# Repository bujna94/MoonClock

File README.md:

### Hi there, I'm Pavol 👋 

### MoonClock website - https://moonclock.com

## You have received and unboxed your MoonClock. Congratulations!

What now?

1. Plug MoonClock into your computer with provided USB-C cable. It will appear as a standard USB drive called "MOONCLOCK".

2. Open "secrets.py" with a text editor such as notepad and replace "WIFI_SSID" and "WIFI_PASSWORD" with your WiFi details and save.

3. Wait ~2minutes until Bitcoin price will appear on the MoonClock device.

That's all!

## Want more Crypto or just adjust the settings?

We all love Bitcoin, sure, but maybe you want to see the current price in another currency or completely another Crypto? No problem. MoonClock is ready for that!

1. Plug MoonClock into your computer with provided USB-C cable. It will appear as a standard USB drive called "MOONCLOCK".

2. Remove all files & folders from the "MOONCLOCK" drive.

3. Configure your cryptocurrencies in conf.py and copy the content of the MOONCLOCK folder to the "MOONCLOCK" USB drive. (Don't forget to change your WiFi details again in the "secrets.py" file if you have to)

Wait ~2 minutes until new crypto will be shown on MoonClock.

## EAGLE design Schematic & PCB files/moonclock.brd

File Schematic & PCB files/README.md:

### The new schematic and PCB design

### Schematic

These are the final schematics using ESP32-S2.

### Main Board:

### USB Board Schematic:

### PCB Design

Here you can see the PCB design currently in manufacture 

### Main Board:

### USB Board:

### PCB view

This is the PCB view from OSH Park (but will be manufactured by JLCPCB).

### Main Board:

### USB Board:

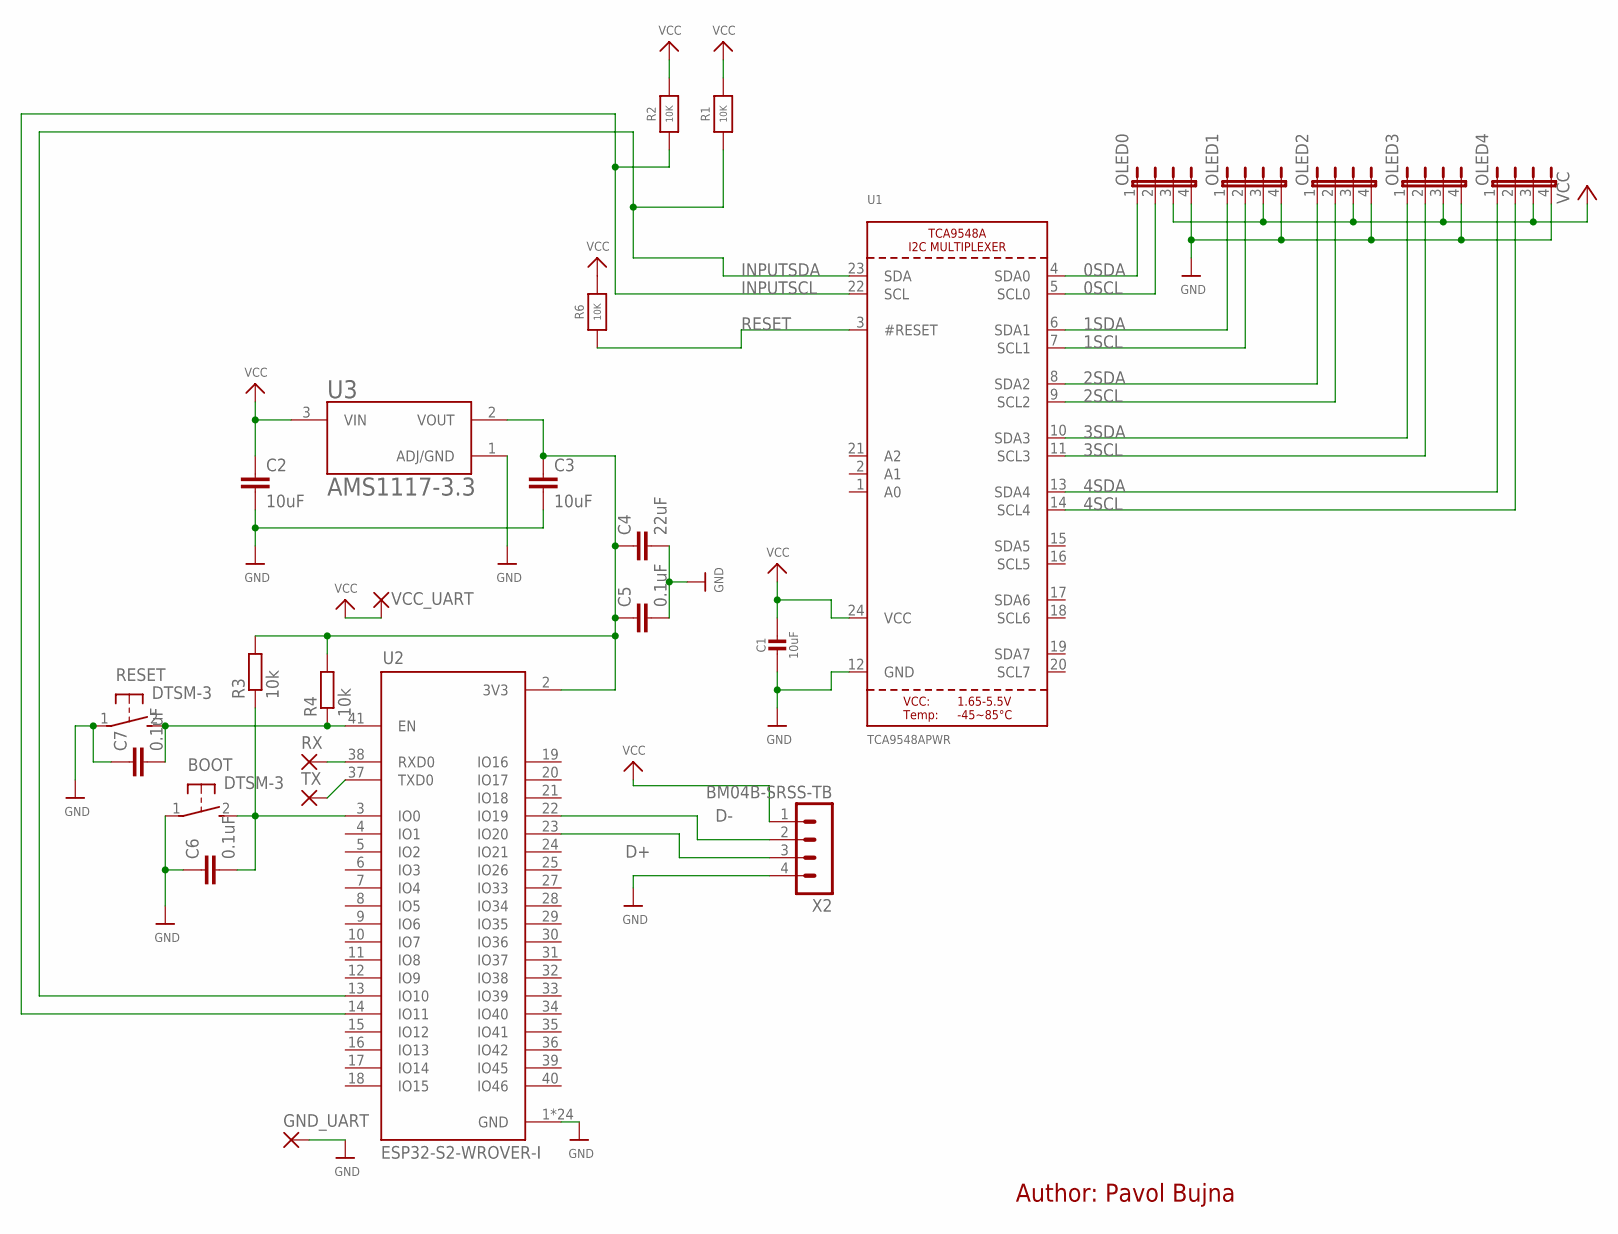
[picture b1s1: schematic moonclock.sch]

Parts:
BOOT: DTSM-3
C1: 10uF; 0805-NO
C2, C3: 10uF; C0805
C4: 22uF; C0805
C5, C6, C7: 0.1uF; C0805
GND_UART: SMD2; SMD1,27-2,54
OLED0, OLED1, OLED2, OLED3, OLED4: JP4E; JP4
R1, R2: 10K; 0805-NO
R3, R4: 10k; R0805
R6: 10K; _0805MP
RESET: DTSM-3
RX: SMD2; SMD1,27-2,54
TX: SMD2; SMD1,27-2,54
U1: TCA9548APWR; TSSOP24
U2: ESP32-S2-WROVER-I
U3: AMS1117-3.3; SOT229P700X180-4N
VCC_UART: SMD2; SMD1,27-2,54
X2: BM04B-SRSS-TB

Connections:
0SCL: OLED0.2, U1.5 (SCL0)
0SDA: OLED0.1, U1.4 (SDA0)
1SCL: OLED1.2, U1.7 (SCL1)
1SDA: OLED1.1, U1.6 (SDA1)
2SCL: OLED2.2, U1.9 (SCL2)
2SDA: OLED2.1, U1.8 (SDA2)
3SCL: OLED3.2, U1.11 (SCL3)
3SDA: OLED3.1, U1.10 (SDA3)
4SCL: OLED4.2, U1.14 (SCL4)
4SDA: OLED4.1, U1.13 (SDA4)
D+: U2.23 (IO20), X2.3
D-: U2.22 (IO19), X2.2
GND: BOOT.1, C1.2, C2.2, C3.2, C4.2, C5.2, C6.1, C7.1, GND_UART.1, OLED0.4, OLED1.4, OLED2.4, OLED3.4, OLED4.4, RESET.1, U1.12 (GND), U2.1 (GND), U2.26 (GND), U2.42 (GND), U2.43.1 (GND), U2.43.2 (GND), U2.43.3 (GND), U2.43.4 (GND), U2.43.5 (GND), U2.43.6 (GND), U2.43.7 (GND), U2.43.8 (GND), U2.43.9 (GND), U2.43.10 (GND), U2.43.11 (GND), U2.43.12 (GND), U2.43.13 (GND), U2.43.14 (GND), U2.43.15 (GND), U2.43.16 (GND), U2.43.17 (GND), U2.43.18 (GND), U2.43.19 (GND), U2.43.20 (GND), U2.43.21 (GND), U3.1 (ADJ/GND), X2.4
INPUTSCL: R2.1, U1.22 (SCL), U2.14 (IO11)
INPUTSDA: R1.1, U1.23 (SDA), U2.13 (IO10)
unnamed: TX.1, U2.37 (TXD0)
unnamed: RX.1, U2.38 (RXD0)
unnamed: C3.1, C4.1, C5.1, R3.2, R4.2, U2.2 (3V3), U3.2 (VOUT)
unnamed: BOOT.2, C6.2, R3.1, U2.3 (IO0)
unnamed: C7.2, R4.1, RESET.2, U2.41 (EN)
RESET: R6.1, U1.3 (#RESET)
VCC: C1.1, C2.1, OLED0.3, OLED1.3, OLED2.3, OLED3.3, OLED4.3, R1.2, R2.2, R6.2, U1.24 (VCC), U3.3 (VIN), VCC_UART.1, X2.1

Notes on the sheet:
Author: Pavol Bujna

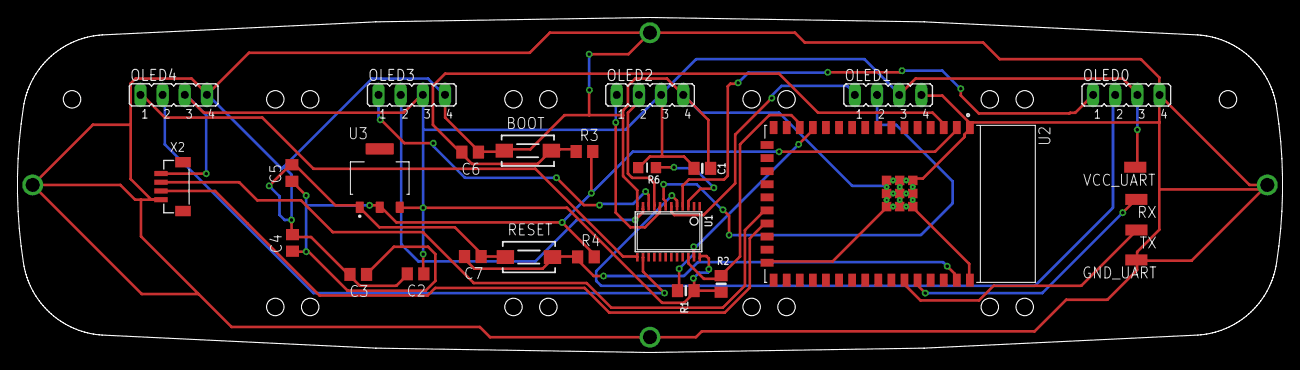
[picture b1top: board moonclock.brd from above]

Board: 2 copper layers, 145.0 x 38.4 mm, 27 parts (0 on the bottom side), 22 nets.

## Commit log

2021-12-08 Added 6 new cryptos & logos screem
    Added folders with codes for 6 different cryptos + screen with logos only.
2021-12-08 Update README.md
    updated IG logo
2021-12-08 Added 6 new cryptocurrencies (USD)
2021-12-08 Added 6 more cryptocurrencies (USD)
2021-12-08 updated BTC logo
2021-12-10 add support for 6-digit block count
2021-12-10 Added Eagle schematic & PCB files
2021-12-10 USD_BAKED-TOKEN added
2021-12-11 added MoonClock website
2021-12-11 fix numbers offset
2021-12-11 my settings
2021-12-12 rotate time, btc, eth, ada
2021-12-12 wait 10 seconds by default
2021-12-12 rename to cycle
2021-12-12 add space between numbers and colon when displaying time
2021-12-12 console print fix
2021-12-12 add cycle and support for all coingecko cryptocurrencies. add conf.py to configure the cycle
2021-12-12 fix DOT to be centered to 54px, add default conf sleep time
2021-12-12 add coingecko api link
2021-12-12 default credentials
2021-12-12 modify readme
2021-12-12 remove unused folders
2021-12-12 remove polkadot from default configuration
2021-12-12 add logos support
2021-12-12 minor improvements
2021-12-13 defined logos examples
2021-12-13 details
2021-12-14 BTC + USD, EUR, GBP added
2021-12-14 Improved rendering performance
2021-12-15 WIP: Refactoring
2021-12-15 Refactoring
2021-12-15 bugfix
2021-12-15 Reworked config. Some minor bugfixes.
2021-12-15 Minor fixes. Changed BTC logo. Added conversion script from .bmp to moonclock format.
2021-12-15 Updated default config
2021-12-15 Renamed CYCLE to MOONCLOCK
2021-12-15 Improved TimeApp
2021-12-15 Fixed timezone
2021-12-15 Changed https back to http
2021-12-15 Added option to hide seconds. Optimized code for disabled seconds.
2021-12-15 typo
2021-12-15 Added time print
2021-12-16 add secrets
2021-12-16 Added secrest.py
2021-12-16 center price of crypto
2021-12-16 Added script that can dopy only the source code files (without conf.py and secrets.py)
2021-12-16 Renamed some vars
2021-12-16 Implented chaging contrast after sunset/sunrise
2021-12-16 Changed order in conf file
2021-12-17 Added datetime library
2021-12-17 Minor fixes and refactoring
2021-12-17 Improved bmp_to_moonclock script
2021-12-17 Generated new symbols.py from original repository
2021-12-17 Updated example conf.py file for BTC maxis
2021-12-17 Improved support for special characters
2021-12-17 Implemented using of special chars
2021-12-18 Added font sources. Fixed number 3, 4, 5 and 7
2021-12-18 Fixed number six
2021-12-18 Fixed number nine
2021-12-18 Added symbol for ALGOrAND
2021-12-18 Added ALGORAND.bmp
2021-12-18 Deleted useless file
2021-12-18 Fixed bmp_to_moonclock.py for different image modes
2021-12-19 Added bitmap generator for fonts
2021-12-19 hotfix
2021-12-19 Reworked font
2021-12-19 Fixed TimeApp
2021-12-19 Added wifi connection retry after fail
2021-12-19 Added back old font
2021-12-19 Added new BTC logo
2021-12-20 Added missing libs
2021-12-20 Added print_exception
2021-12-21 Increased I2C frequency to 1400000
2021-12-22 Added alphabet chars
2021-12-22 Added alphabet chars to font.py
2021-12-22 fix letters and add more symbols
2021-12-22 add text, fees, halving, blockheight
2021-12-22 fix price with 7 places, round to 4 decimals
2021-12-23 add more wifi networks support, show ugly "connecting to wifi"
2021-12-23 change secrets to array
2021-12-23 only use one wifi setting by default
2021-12-23 use only one network by default
2021-12-23 Code cleanup
2021-12-23 Added sleep(1) to wifi connection phase
2021-12-23 add wifi setup, fix logos with transparent spaces
2021-12-25 reload MC when app crashes
2021-12-25 fix hexa numbers, format
2021-12-25 add support for left, right, center alignment, fix halving string
2021-12-29 add two more apps difficulty, temperature
2021-12-29 add default update frequency to duration time
2021-12-29 formatting
2021-12-30 Reformat
2021-12-30 Reverted default secrets.py
2021-12-30 Removed duplicate key from confinguration
2021-12-30 Reformatted imports
2021-12-30 btx maxi conf ofc
2021-12-30 fix str_align to str_rjust
2022-01-02 fix weather app when some arg is None, add update frequency to CryptoApp
2022-01-03 add support for configurable decimals, add EXPERIMENTAL app Xpub (accepts xpub, ypub, zpub)
2022-01-03 add test app to turn on all displays
2022-01-03 add support also for fill with zeros to test app
2022-01-03 add moscow char at the beggining and the end of moscow time app
2022-01-04 fix missing symbols check and cross
2022-01-04 minor adjustments
2022-01-06 add Lnbits wallet app
2022-01-07 use port from configuration
2022-01-09 Fixed app duration and update_frequency
2022-01-09 Reworked datetime
2022-01-10 Removed timezones from apps
2022-01-10 Changed time API from http to https
2022-01-10 Added datetime lazy loading
2022-01-10 Removed debug print
2022-01-10 Removed wifi networks scanning
2022-01-11 Added support for multiple timezones. Added integrity check script. Changed all https to http, because it seems to be more stable.
2022-01-12 Changed RESET text
2022-01-12 Fixed conf.py
2022-01-12 Replaced all https to http
2022-01-12 Coingecko doesnt support http
2022-01-13 Added timeout to all request calls
2022-01-17 Probably fixed freezing? :thinking:
2022-01-17 Added more debug print
2022-01-17 Added more debug prints
2022-01-17 Changed time api to timeapi.io
2022-01-17 another fix
2022-01-19 fix decimals
2022-01-20 Code formatting
2022-01-20 Implemented NTP
2022-01-21 Added VERASITY and THORCHAIN logos
2022-01-21 Added thounsands separator support
2022-01-21 Added ALGORAND logo. Added new crypto logos to marketcap application.
2022-01-21 Modified VERASITY logo
2022-01-21 Added more decimals for low-cost cryptos
2022-01-22 Added support for conf.json
2022-01-27 Implemented more generic logo handling
2022-01-27 Converted input params to lowercase
2022-01-27 Adde default param to get_logos
2022-01-29 Added support for multiple crypto apis
2022-01-29 Added kucoin
2022-01-30 Implemented latlng
2022-01-30 Added conf error
2022-01-30 Simplified lambda expression
2022-01-30 Forgot to call show()
2022-01-30 added raise
2022-01-30 Moved conf load before wifi init
2022-01-30 Fixed FTX
2022-04-18 Added WIFI INIT message
2022-11-23 Added logo of Monero
    Fix
2024-09-27 use binance API

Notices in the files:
parts and their libraries:
microbuilder: This work is placed in the public domain, and may be freely used for commercial and non-commercial work with the following conditions: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
